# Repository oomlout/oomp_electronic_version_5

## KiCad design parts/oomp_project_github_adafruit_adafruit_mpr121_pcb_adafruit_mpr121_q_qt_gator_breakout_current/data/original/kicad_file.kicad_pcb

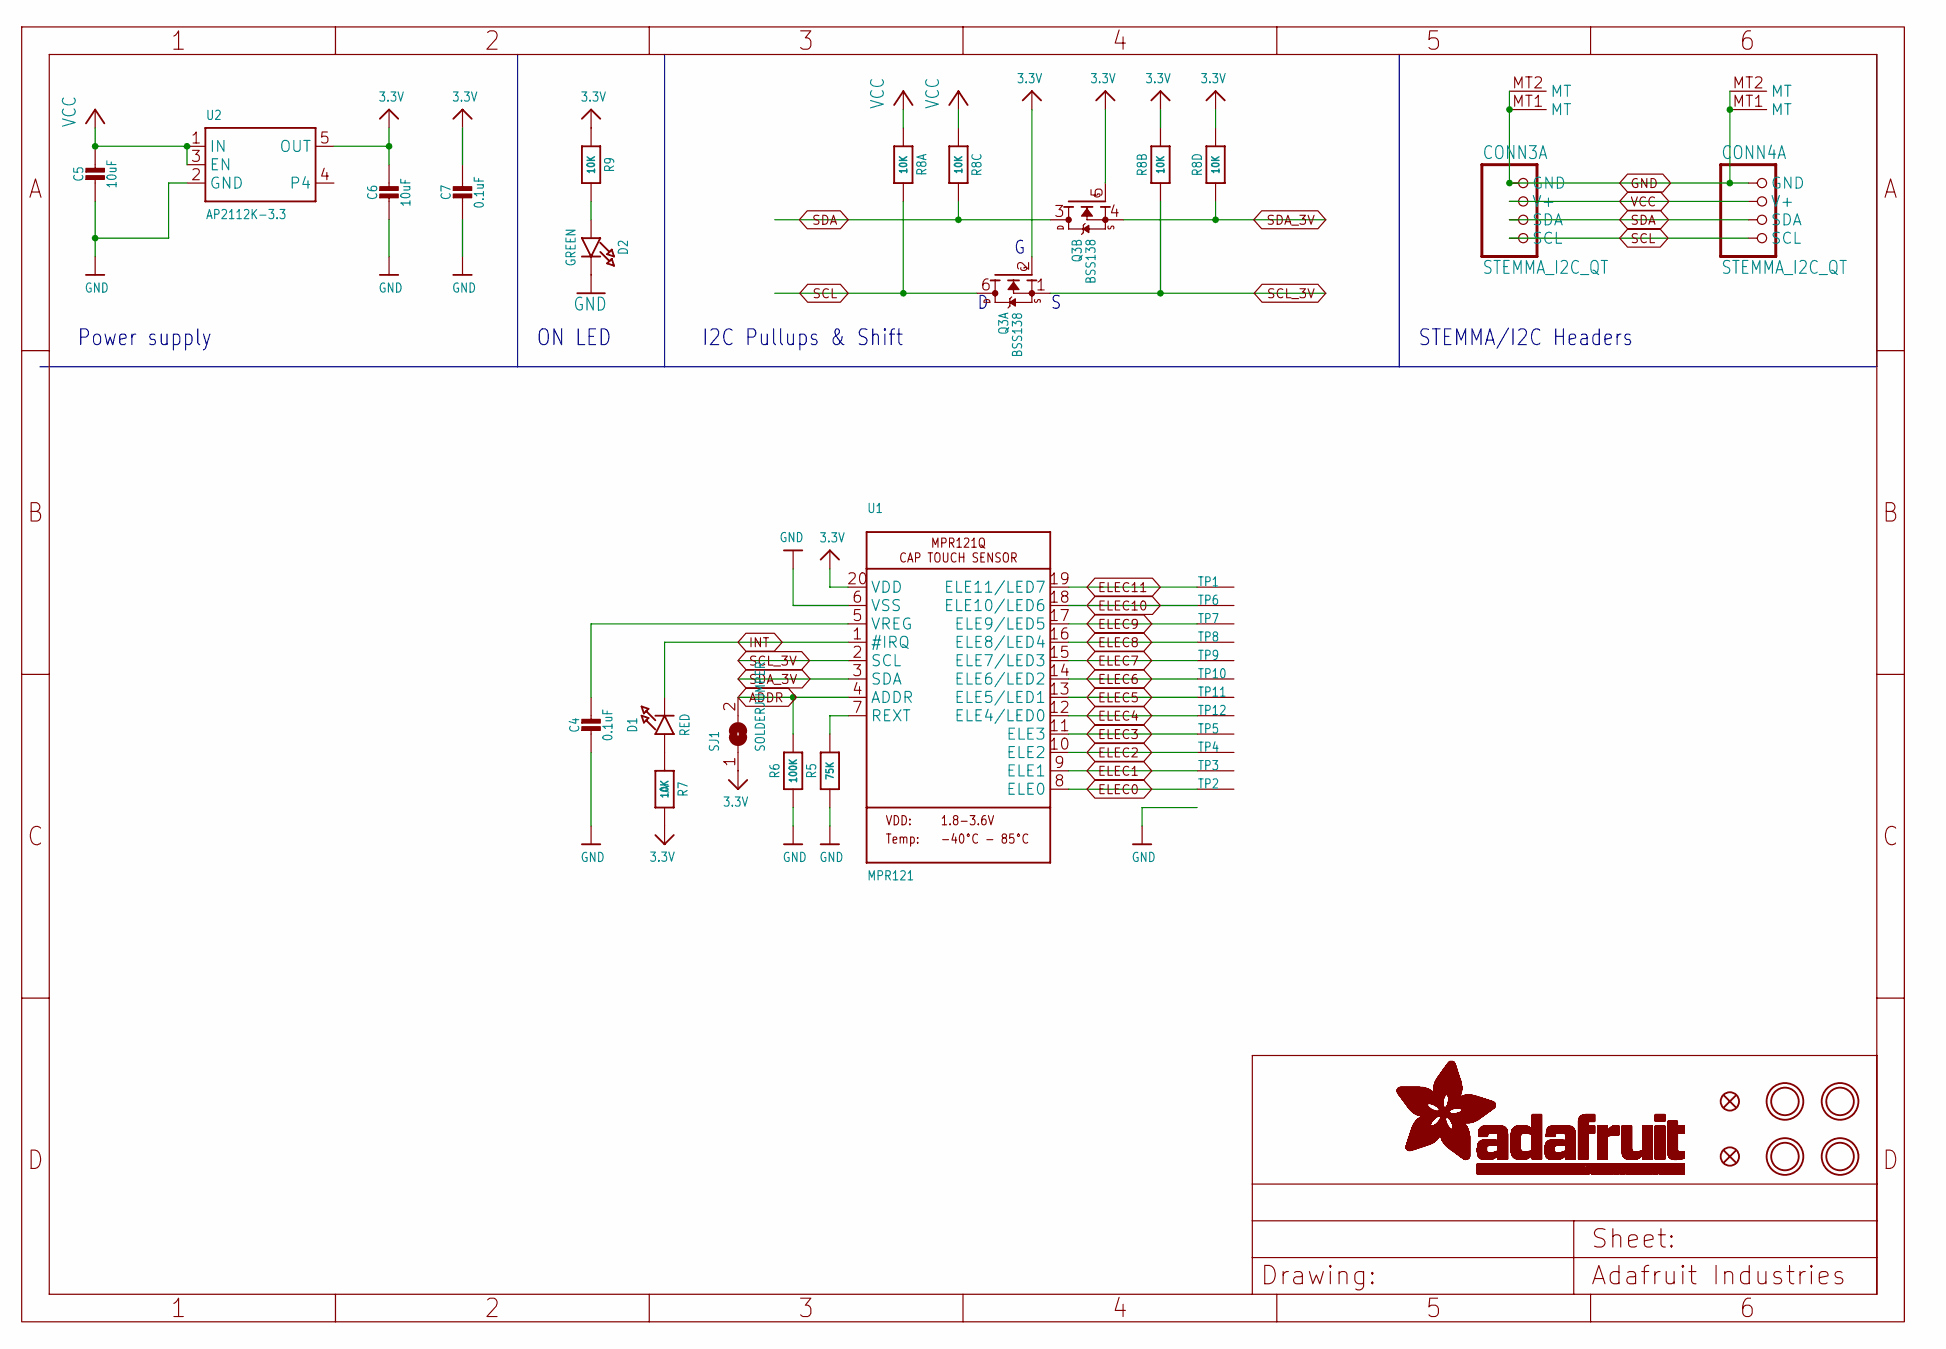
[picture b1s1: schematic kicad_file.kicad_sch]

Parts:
C4, C7: 0.1uF; 0603-NO
C5, C6: 10uF; 0805-NO
CONN3, CONN4: STEMMA_I2C_QT; JST_SH4
D1: RED; CHIPLED_0603_NOOUTLINE
D2: GREEN; CHIPLED_0603_NOOUTLINE
FID3, FID4: FIDUCIAL_1MM
Q3: BSS138; SOT363
R5: 75K; 0603-NO
R6: 100K; 0603-NO
R7, R9: 10K; 0603-NO
R8: 10K; RESPACK_4X0603
SJ1: SOLDERJUMPER; SOLDERJUMPER_ARROW_NOPASTE
TP1, TP2, TP3, TP4, TP5, TP6, TP7, TP8, TP9, TP10, TP11, TP12: SEWTAPPCB_ALLIGATOR; PCB_ALLI
U1: MPR121; QFN20_3MM_NOTHERMAL
U2: AP2112K-3.3; SOT23-5
U$7, U$8, U$34, U$35: MOUNTINGHOLE2.5; MOUNTINGHOLE_2.5_PLATED

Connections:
3.3V: C6.1, C7.1, Q3.2 (G), Q3.5 (G), R7.2, R8.2 (1), R8.4 (1), R9.1, SJ1.1, U1.20 (VDD), U2.5 (OUT)
ADDR: R6.2, SJ1.2, U1.4 (ADDR)
ELEC0: TP2.P$1, U1.8 (ELE0)
ELEC1: TP3.P$1, U1.9 (ELE1)
ELEC2: TP4.P$1, U1.10 (ELE2)
ELEC3: TP5.P$1, U1.11 (ELE3)
ELEC4: TP12.P$1, U1.12 (ELE4/LED0)
ELEC5: TP11.P$1, U1.13 (ELE5/LED1)
ELEC6: TP10.P$1, U1.14 (ELE6/LED2)
ELEC7: TP9.P$1, U1.15 (ELE7/LED3)
ELEC8: TP8.P$1, U1.16 (ELE8/LED4)
ELEC9: TP7.P$1, U1.17 (ELE9/LED5)
ELEC10: TP6.P$1, U1.18 (ELE10/LED6)
ELEC11: TP1.P$1, U1.19 (ELE11/LED7)
GND: C4.2, C5.2, C6.2, C7.2, CONN3.1 (GND), CONN3.MT1 (MT), CONN3.MT2 (MT), CONN4.1 (GND), CONN4.MT1 (MT), CONN4.MT2 (MT), D2.C, R5.1, R6.1, U1.6 (VSS), U2.2 (GND)
INT: D1.C, U1.1 (#IRQ)
unnamed: D1.A, R7.1
unnamed: C4.1, U1.5 (VREG)
unnamed: R5.2, U1.7 (REXT)
unnamed: D2.A, R9.2
SCL: CONN3.4 (SCL), CONN4.4 (SCL), Q3.6 (D), R8.8 (2)
SCL_3V: Q3.1 (S), R8.7 (2), U1.2 (SCL)
SDA: CONN3.3 (SDA), CONN4.3 (SDA), Q3.3 (D), R8.6 (2)
SDA_3V: Q3.4 (S), R8.5 (2), U1.3 (SDA)
VCC: C5.1, CONN3.2 (V+), CONN4.2 (V+), R8.1, R8.3 (1), U2.1 (IN), U2.3 (EN)

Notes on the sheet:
ON LED
I2C Pullups & Shift
STEMMA/I2C Headers
Power supply

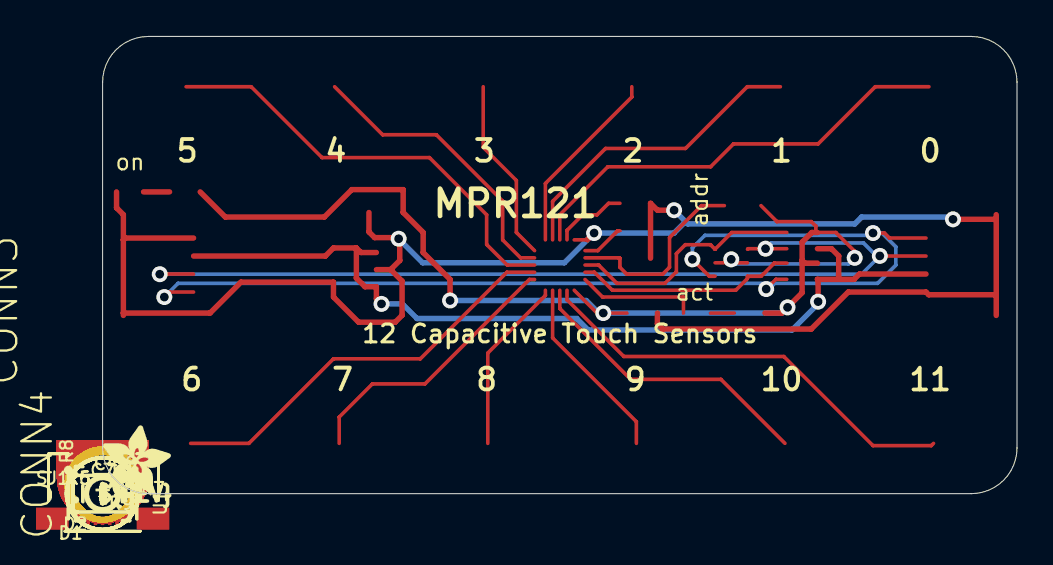
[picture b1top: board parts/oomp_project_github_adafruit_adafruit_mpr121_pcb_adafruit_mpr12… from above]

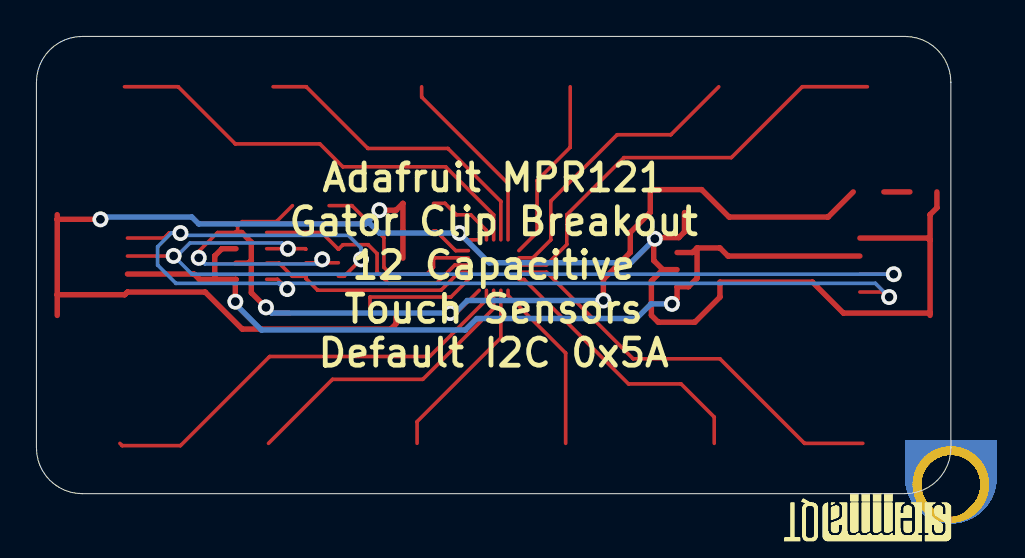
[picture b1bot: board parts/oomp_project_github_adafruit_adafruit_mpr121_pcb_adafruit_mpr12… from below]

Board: 2 copper layers, 50.8 x 25.4 mm, 39 parts (2 on the bottom side), 25 nets.

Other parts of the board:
U$10: PCBFEAT-REV-040
U$37: ADAFRUIT_3.5MM
U$39, U$40: STEMMAQT

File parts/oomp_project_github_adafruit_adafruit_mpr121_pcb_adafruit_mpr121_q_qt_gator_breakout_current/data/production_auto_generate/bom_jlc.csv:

Comment,Designator,Footprint,LCSC Part #
,U$37,Adafruit MPR121Q QT Gator Breakout-import-fps:ADAFRUIT_3.5MM,
,U$10,Adafruit MPR121Q QT Gator Breakout-import-fps:PCBFEAT-REV-040,
,"U$39,U$40",Adafruit MPR121Q QT Gator Breakout-import-fps:STEMMAQT,
0.1uF,"C4,C7",Adafruit MPR121Q QT Gator Breakout-import-fps:0603-NO,C14663
100K,R6,Adafruit MPR121Q QT Gator Breakout-import-fps:0603-NO,C25803
10K,"R7,R9",Adafruit MPR121Q QT Gator Breakout-import-fps:0603-NO,C98220
10K,R8,Adafruit MPR121Q QT Gator Breakout-import-fps:RESPACK_4X0603,C98220
10uF,"C5,C6",Adafruit MPR121Q QT Gator Breakout-import-fps:0805-NO,
75K,R5,Adafruit MPR121Q QT Gator Breakout-import-fps:0603-NO,C2907067
AP2112K-3.3,U2,Adafruit MPR121Q QT Gator Breakout-import-fps:SOT23-5,
BSS138,Q3,Adafruit MPR121Q QT Gator Breakout-import-fps:SOT363,
GREEN,D2,Adafruit MPR121Q QT Gator Breakout-import-fps:CHIPLED_0603_NOOUTLINE,
MPR121,U1,Adafruit MPR121Q QT Gator Breakout-import-fps:QFN20_3MM_NOTHERMAL,
RED,D1,Adafruit MPR121Q QT Gator Breakout-import-fps:CHIPLED_0603_NOOUTLINE,
STEMMA_I2C_QT,"CONN3,CONN4",Adafruit MPR121Q QT Gator Breakout-import-fps:JST_SH4,C160404

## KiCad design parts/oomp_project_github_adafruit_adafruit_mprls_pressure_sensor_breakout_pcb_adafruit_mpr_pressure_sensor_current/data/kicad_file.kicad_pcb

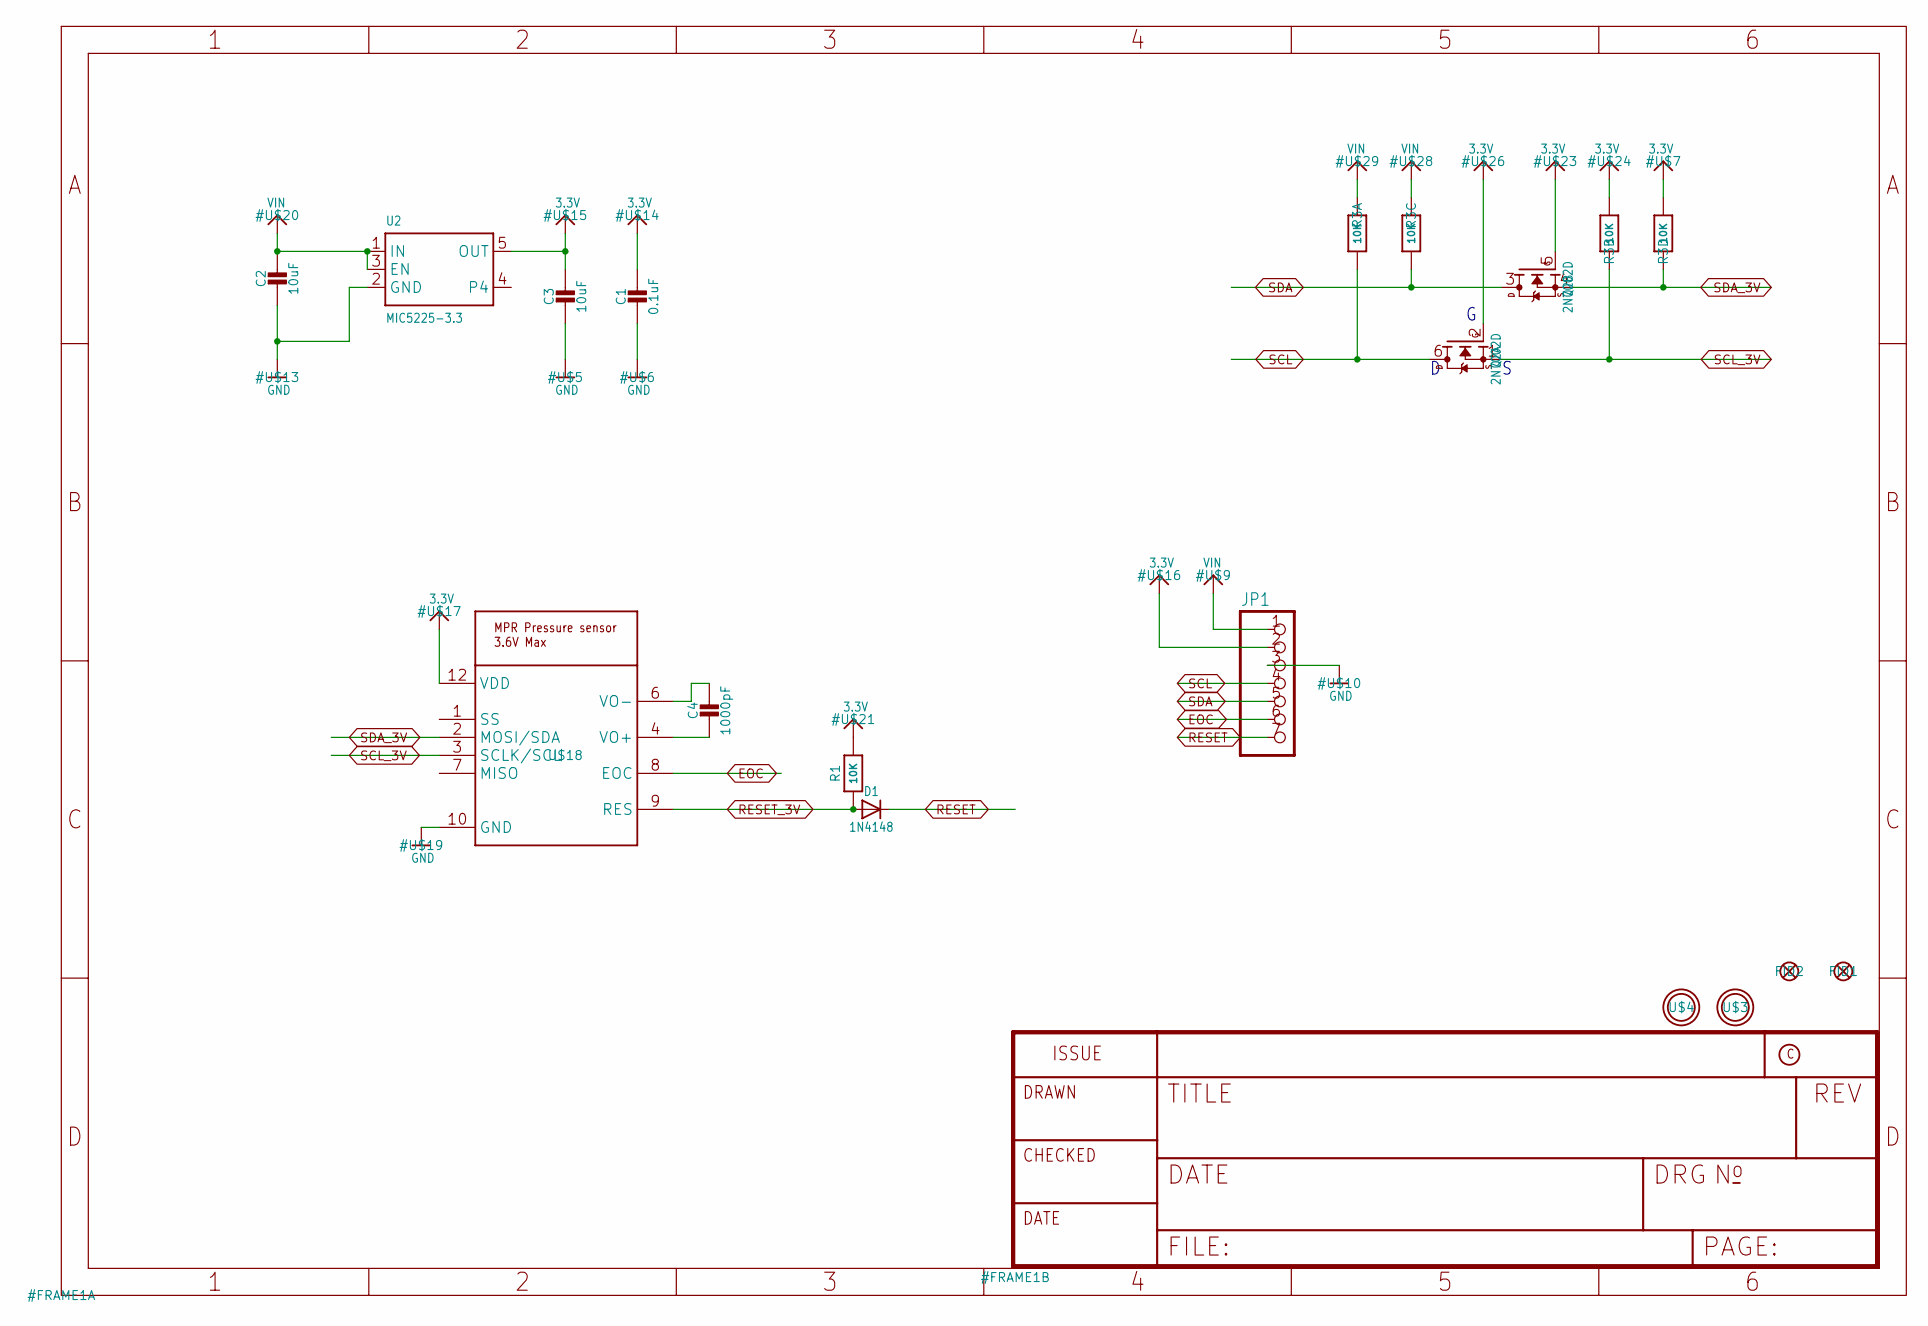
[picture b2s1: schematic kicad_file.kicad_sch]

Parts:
C1: 0.1uF; 0603-NO
C2, C3: 10uF; 0805-NO
C4: 1000pF; 0603-NO
D1: 1N4148; SOD-323
FID1, FID2: FIDUCIAL_1MM
JP1: HEADER-1X770MIL; 1X07_ROUND_70
Q2: 2N7002D; SOT363
R1: 10K; 0603-NO
R3: 10K; RESPACK_4X0603
U2: MIC5225-3.3; SOT23-5
U$3, U$4: MOUNTINGHOLE2.5; MOUNTINGHOLE_2.5_PLATED
U$18: MPR_SERIES_I2C_PRESSURE

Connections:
3.3V: C1.1, C3.1, JP1.2, Q2.2 (G), Q2.5 (G), R1.2, R3.2 (1), R3.4 (1), U2.5 (OUT), U$18.12 (VDD)
EOC: JP1.6, U$18.8 (EOC)
GND: C1.2, C2.2, C3.2, JP1.3, U2.2 (GND), U$18.10 (GND)
unnamed: C4.2, U$18.4 (VO+)
unnamed: C4.1, U$18.6 (VO-)
RESET: D1.C, JP1.7
RESET_3V: D1.A, R1.1, U$18.9 (RES)
SCL: JP1.4, Q2.6 (D), R3.8 (2)
SCL_3V: Q2.1 (S), R3.7 (2), U$18.3 (SCLK/SCL)
SDA: JP1.5, Q2.3 (D), R3.6 (2)
SDA_3V: Q2.4 (S), R3.5 (2), U$18.2 (MOSI/SDA)
VIN: C2.1, JP1.1, R3.1, R3.3 (1), U2.1 (IN), U2.3 (EN)

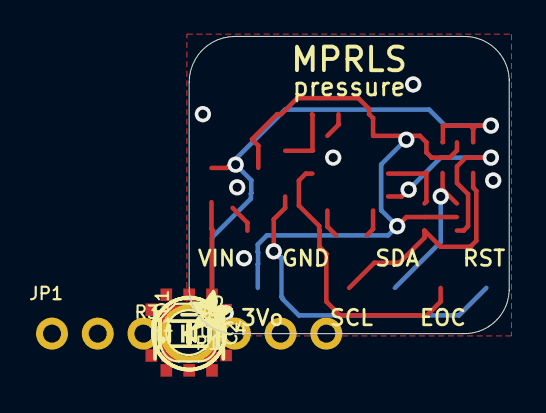
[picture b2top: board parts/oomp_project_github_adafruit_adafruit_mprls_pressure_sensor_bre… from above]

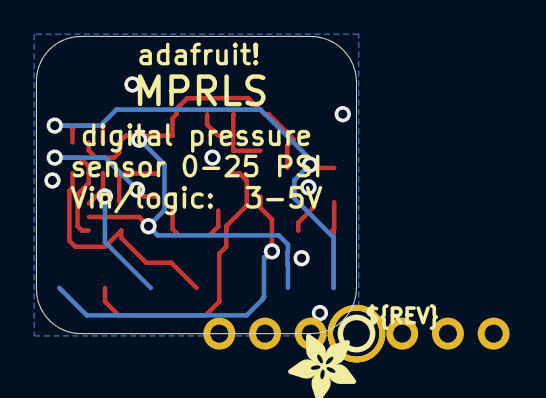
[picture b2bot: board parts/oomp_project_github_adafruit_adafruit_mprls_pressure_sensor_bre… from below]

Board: 2 copper layers, 17.8 x 16.5 mm, 18 parts (2 on the bottom side), 12 nets.

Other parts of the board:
U$1: ADAFRUIT_3.5MM
U$8: ADAFRUIT_2.5MM
U$27: PCBFEAT-REV-040

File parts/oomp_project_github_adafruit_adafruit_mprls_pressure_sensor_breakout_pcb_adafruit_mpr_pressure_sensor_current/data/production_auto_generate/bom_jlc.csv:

Comment,Designator,Footprint,LCSC Part #
,JP1,Adafruit MPR pressure sensor-import-fps:1X07_ROUND_70,C7501585
,U$8,Adafruit MPR pressure sensor-import-fps:ADAFRUIT_2.5MM,
,U$1,Adafruit MPR pressure sensor-import-fps:ADAFRUIT_3.5MM,
,U$27,Adafruit MPR pressure sensor-import-fps:PCBFEAT-REV-040,
0.1uF,C1,Adafruit MPR pressure sensor-import-fps:0603-NO,C14663
1000pF,C4,Adafruit MPR pressure sensor-import-fps:0603-NO,
10K,R1,Adafruit MPR pressure sensor-import-fps:0603-NO,C98220
10K,R3,Adafruit MPR pressure sensor-import-fps:RESPACK_4X0603,C98220
10uF,"C2,C3",Adafruit MPR pressure sensor-import-fps:0805-NO,
1N4148,D1,Adafruit MPR pressure sensor-import-fps:SOD-323,
2N7002D,Q2,Adafruit MPR pressure sensor-import-fps:SOT363,
MIC5225-3.3,U2,Adafruit MPR pressure sensor-import-fps:SOT23-5,
MPR_SERIES_I2C_PRESSURE,U$18,Adafruit MPR pressure sensor-import-fps:MPR_SERIES_I2C_PRESSURE,

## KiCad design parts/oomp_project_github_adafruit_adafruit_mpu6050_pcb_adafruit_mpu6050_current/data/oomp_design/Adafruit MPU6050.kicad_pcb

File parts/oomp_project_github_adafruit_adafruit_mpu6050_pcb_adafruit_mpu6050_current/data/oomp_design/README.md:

# OOMP KiCad design copy

Open `Adafruit MPU6050.kicad_pro` (or the `.kicad_pcb` / `.kicad_sch`) in KiCad. Local OOMP libraries are under `libraries/`. Original inputs are preserved in [../original/](../original/).

Only verified unchanged installed KiCad defaults were renamed. Modified, custom, unmatched and unavailable items remain unchanged. Soldering variants are never swapped during conversion. Existing pad coordinates, nets and UUIDs are preserved.

See [conversion_report.yaml](conversion_report.yaml) for every conversion and skip. Copy this directory before editing; regeneration refuses to overwrite edited design files.

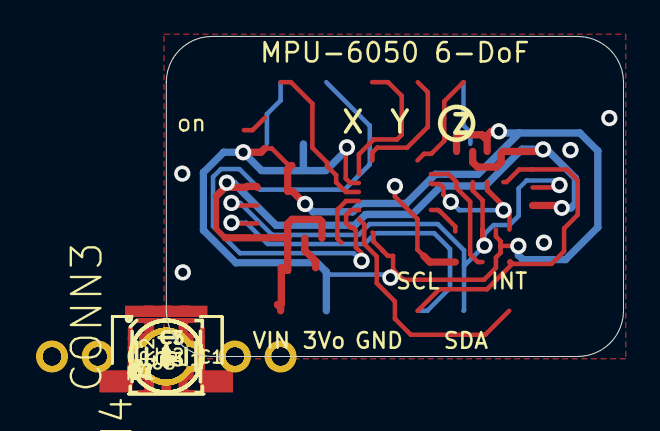
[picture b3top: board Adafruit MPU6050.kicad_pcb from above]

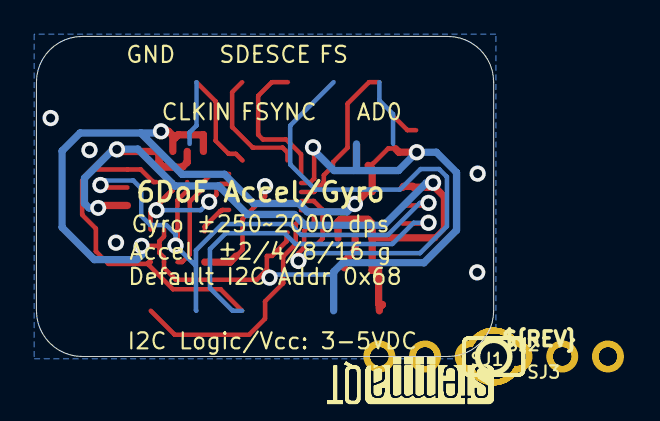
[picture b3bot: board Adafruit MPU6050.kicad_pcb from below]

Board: 2 copper layers, 25.4 x 17.8 mm, 28 parts (6 on the bottom side), 16 nets.

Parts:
C1: 2.2nF; 0603-NO
C2, C7: 0.1uF; 0603-NO
C5, C6: 10uF; 0805-NO
CONN3, CONN4: STEMMA_I2C_QT; JST_SH4
D1: GREEN; CHIPLED_0603_NOOUTLINE
FID3, FID4: FIDUCIAL_1MM
JP2: 1X06_ROUND
JP3: 1X06_ROUND_70
Q2: BSS138; SOT363
R2, R4: 10K; 0603-NO
R3: 10K; RESPACK_4X0603
SJ1: CLKIN; SOLDERJUMPER_CLOSEDWIRE
SJ2: FSYNC; SOLDERJUMPER_CLOSEDWIRE
SJ3: SOLDERJUMPER_ARROW_NOPASTE
U1: MPU-6050; QFN24_4MM_SMSC
U3: AP2112K-3.3; SOT23-5
U$39, U$40, U$42, U$43: MOUNTINGHOLE2.5; MOUNTINGHOLE_2.5_PLATED
U$46: PCBFEAT-REV-040
U$47, U$48: STEMMAQT

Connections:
3.3V: C6.1, C7.1, JP3.2, Q2.2, Q2.5, R3.2, R3.4, R4.1, SJ3.1, U1.8, U1.13, U3.5
AD0: JP2.1, R2.1, SJ3.2, U1.9
CLKIN: JP2.5, SJ1.2, U1.1
CPOUT: C1.1, U1.20
FSYNC_IN: JP2.2, SJ2.2, U1.11
GND: C1.2, C2.2, C5.2, C6.2, C7.2, CONN3.1, CONN4.1, D1.C, JP2.6, JP3.3, R2.2, SJ1.1, SJ2.1, U1.18, U1.THERM, U3.2
INT: JP3.6, U1.12
unnamed: D1.A, R4.2
REGOUT: C2.1, U1.10
SCL: CONN3.4, CONN4.4, JP3.4, Q2.6, R3.8
SCL_3V: Q2.1, R3.7, U1.23
SCL_EXT: JP2.3, U1.7
SDA: CONN3.3, CONN4.3, JP3.5, Q2.3, R3.6
SDA_3V: Q2.4, R3.5, U1.24
SDA_EXT: JP2.4, U1.6
VCC: C5.1, CONN3.2, CONN4.2, JP3.1, R3.1, R3.3, U3.1, U3.3

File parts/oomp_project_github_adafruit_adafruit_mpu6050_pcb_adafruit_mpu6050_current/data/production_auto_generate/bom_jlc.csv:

Comment,Designator,Footprint,LCSC Part #
,JP2,Adafruit MPU6050-import-fps:1X06_ROUND,C37208
,JP3,Adafruit MPU6050-import-fps:1X06_ROUND_70,C37208
,U$46,Adafruit MPU6050-import-fps:PCBFEAT-REV-040,
,"U$47,U$48",Adafruit MPU6050-import-fps:STEMMAQT,
0.1uF,"C2,C7",Adafruit MPU6050-import-fps:0603-NO,C14663
10K,"R2,R4",Adafruit MPU6050-import-fps:0603-NO,C98220
10K,R3,Adafruit MPU6050-import-fps:RESPACK_4X0603,C98220
10uF,"C5,C6",Adafruit MPU6050-import-fps:0805-NO,
2.2nF,C1,Adafruit MPU6050-import-fps:0603-NO,
AP2112K-3.3,U3,Adafruit MPU6050-import-fps:SOT23-5,
BSS138,Q2,Adafruit MPU6050-import-fps:SOT363,
GREEN,D1,Adafruit MPU6050-import-fps:CHIPLED_0603_NOOUTLINE,
MPU-6050,U1,Adafruit MPU6050-import-fps:QFN24_4MM_SMSC,
STEMMA_I2C_QT,"CONN3,CONN4",Adafruit MPU6050-import-fps:JST_SH4,C160404

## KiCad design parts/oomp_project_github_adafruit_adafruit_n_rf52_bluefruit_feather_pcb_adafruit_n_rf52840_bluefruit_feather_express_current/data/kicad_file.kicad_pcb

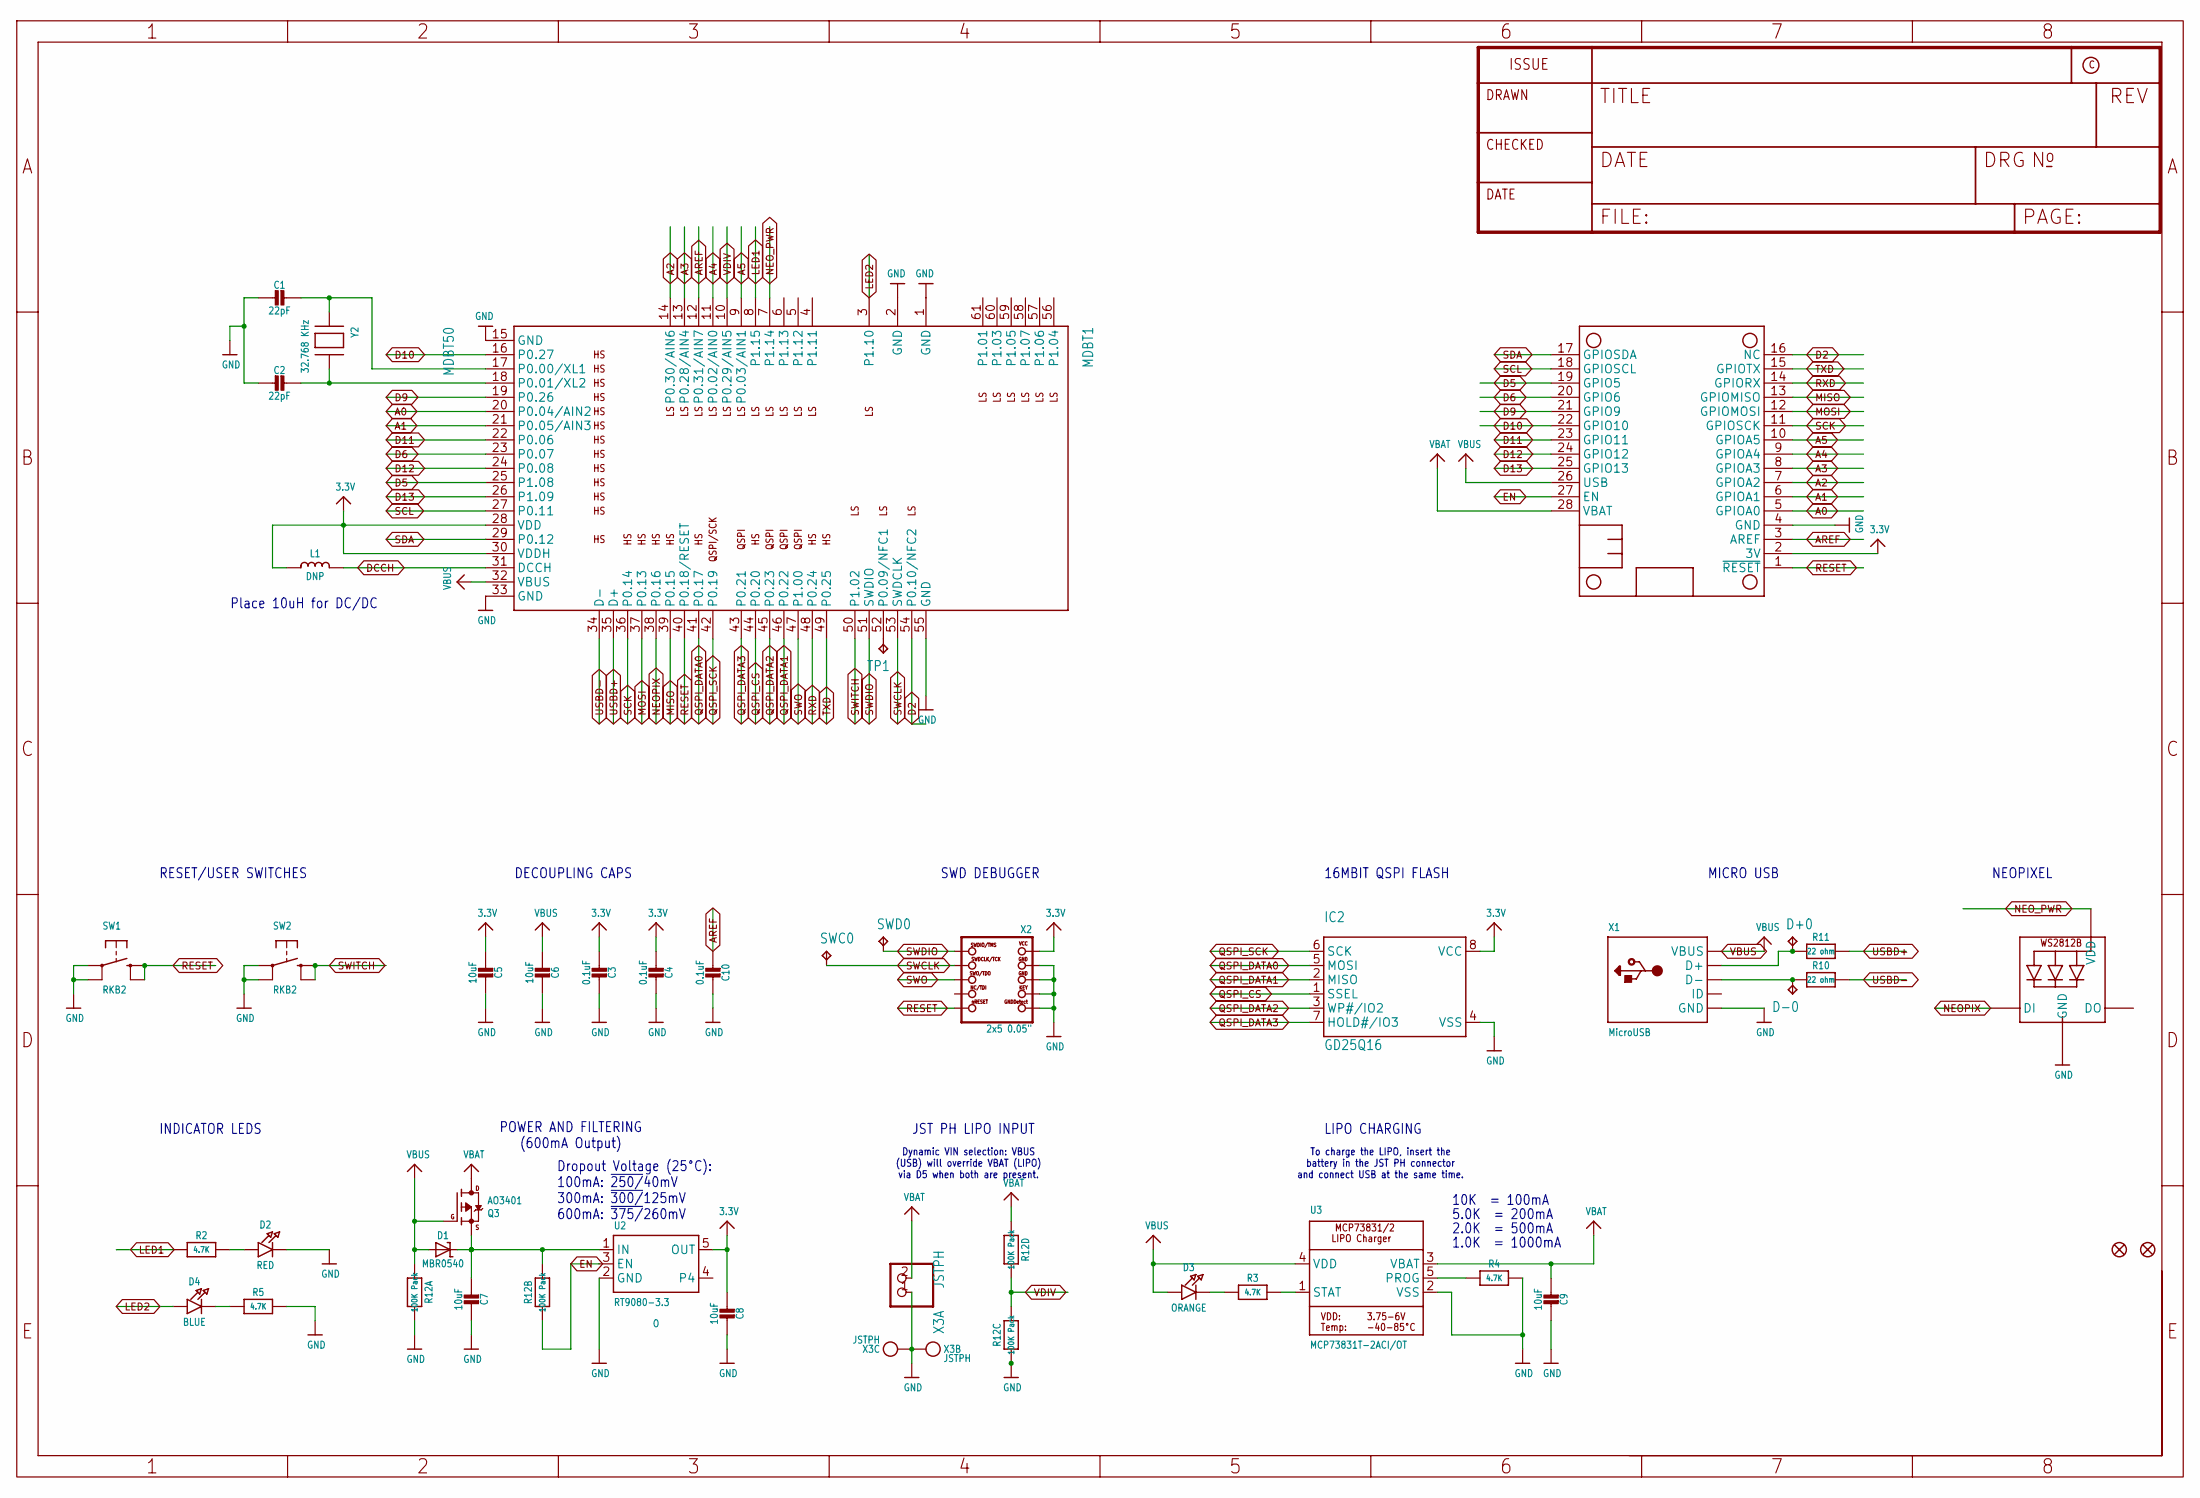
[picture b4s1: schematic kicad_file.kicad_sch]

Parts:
C1, C2: 22pF; 0603-NO
C3, C4, C10: 0.1uF; 0603-NO
C5, C6, C7, C8, C9: 10uF; 0805-NO
D1: MBR0540; SOD-123
D2: RED; CHIPLED_0603_NOOUTLINE
D3: ORANGE; CHIPLED_0603_NOOUTLINE
D4: BLUE; CHIPLED_0603_NOOUTLINE
D+0: TPTP10R; TP10R
D-0: TPTP10R; TP10R
FID1, FID2: FIDUCIAL_1MM
IC2: GD25Q16; USON8
L1: DNP; _0805MP
LED1: WS2812B_3535FULL; LED3535_FULLPADS
MDBT1: MDBT50
MS1: FEATHERWING_NODIM
Q3: AO3401; SOT23-R
R2, R3, R4, R5: 4.7K; 0603-NO
R10, R11: 22 ohm; _0603MP
R12: 100K Pack; RESPACK_4X0603
SW1, SW2: RKB2; BTN_RKB2_4.6X2.8
SWC0: TPTP12R; TP12R
SWD0: TPTP12R; TP12R
TP1: TPTP10R; TP10R
U2: RT9080-3.3; SOT23-5; JLC_ROTATION 0
U3: MCP73831T-2ACI/OT; SOT23-5; JLC_ROTATION 0
X1: MicroUSB; 4UCONN_20329_V2
X2: 2x5 0.05"; 2X05_1.27MM_BOX_POSTS
X3: JSTPH; JSTPH2_BATT; LCSC C47647
Y2: 32.768 KHz; XTAL3215

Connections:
3.3V: C3.2, C4.2, C5.2, C8.2, IC2.8 (VCC), L1.1, MDBT1.28 (VDD), MDBT1.30 (VDDH), MS1.2 (3V), U2.5 (OUT), X2.1 (VCC)
A0: MDBT1.20 (P0.04/AIN2), MS1.5 (GPIOA0)
A1: MDBT1.21 (P0.05/AIN3), MS1.6 (GPIOA1)
A2: MDBT1.14 (P0.30/AIN6), MS1.7 (GPIOA2)
A3: MDBT1.13 (P0.28/AIN4), MS1.8 (GPIOA3)
A4: MDBT1.11 (P0.02/AIN0), MS1.9 (GPIOA4)
A5: MDBT1.9 (P0.03/AIN1), MS1.10 (GPIOA5)
AREF: C10.2, MDBT1.12 (P0.31/AIN7), MS1.3 (AREF)
D2: MDBT1.54 (P0.10/NFC2), MS1.16 (NC)
D5: MDBT1.25 (P1.08), MS1.19 (GPIO5)
D6: MDBT1.23 (P0.07), MS1.20 (GPIO6)
D9: MDBT1.19 (P0.26), MS1.21 (GPIO9)
D10: MDBT1.16 (P0.27), MS1.22 (GPIO10)
D11: MDBT1.22 (P0.06), MS1.23 (GPIO11)
D12: MDBT1.24 (P0.08), MS1.24 (GPIO12)
D13: MDBT1.26 (P1.09), MS1.25 (GPIO13)
D+: D+0.TP, R11.1, X1.D+
D-: D-0.TP, R10.1, X1.D-
DCCH: L1.2, MDBT1.31 (DCCH)
EN: MS1.27 (EN), R12.2 (1), U2.3 (EN)
GND: C1.2, C2.2, C3.1, C4.1, C5.1, C6.1, C7.1, C8.1, C9.1, C10.1, D2.C, IC2.4 (VSS), LED1.4 (GND), MDBT1.1 (GND), MDBT1.2 (GND), MDBT1.15 (GND), MDBT1.33 (GND), MDBT1.55 (GND), MS1.4 (GND), R4.2, R5.2, R12.3 (1), R12.8 (2), SW1.A, SW1.A' (P1), SW2.A, SW2.A' (P1), U2.2 (GND), U3.2 (VSS), X1.BASE@1 (GND), X1.BASE@2 (GND), X1.GND, X1.SPRT@1 (GND), X1.SPRT@2 (GND), X1.SPRT@3 (GND), X1.SPRT@4 (GND), X2.3 (GND), X2.5 (GND), X2.7 (KEY), X2.9 (GNDDETECT), X3.1, X3.NC1, X3.NC2
LED1: MDBT1.8 (P1.15), R2.1
LED2: D4.A, MDBT1.3 (P1.10)
MISO: MDBT1.39 (P0.15), MS1.13 (GPIOMISO)
MOSI: MDBT1.37 (P0.13), MS1.12 (GPIOMOSI)
unnamed: D3.C, R3.1
unnamed: D2.A, R2.2
unnamed: C1.1, MDBT1.17 (P0.00/XL1), Y2.P$1
unnamed: C2.1, MDBT1.18 (P0.01/XL2), Y2.P$2
unnamed: R3.2, U3.1 (STAT)
unnamed: R4.1, U3.5 (PROG)
unnamed: D4.C, R5.1
NEOPIX: LED1.1 (DI), MDBT1.38 (P0.16)
NEO_PWR: LED1.2 (VDD), MDBT1.7 (P1.14)
NFC2: MDBT1.52 (P0.09/NFC1), TP1.TP
QSPI_CS: IC2.1 (SSEL), MDBT1.44 (P0.20)
QSPI_DATA0: IC2.5 (MOSI), MDBT1.41 (P0.17)
QSPI_DATA1: IC2.2 (MISO), MDBT1.46 (P0.22)
QSPI_DATA2: IC2.3 (WP#/IO2), MDBT1.45 (P0.23)
QSPI_DATA3: IC2.7 (HOLD#/IO3), MDBT1.43 (P0.21)
QSPI_SCK: IC2.6 (SCK), MDBT1.42 (P0.19)
RESET: MDBT1.40 (P0.18/RESET), MS1.1 (~RESET), SW1.B (S), SW1.B' (S1), X2.10 (NRESET)
RXD: MDBT1.48 (P0.24), MS1.14 (GPIORX)
SCK: MDBT1.36 (P0.14), MS1.11 (GPIOSCK)
SCL: MDBT1.27 (P0.11), MS1.18 (GPIOSCL)
SDA: MDBT1.29 (P0.12), MS1.17 (GPIOSDA)
SWCLK: MDBT1.53 (SWDCLK), SWC0.TP, X2.4 (SWDCLK)
SWDIO: MDBT1.51 (SWDIO), SWD0.TP, X2.2 (SWDIO)
SWITCH: MDBT1.50 (P1.02), SW2.B (S), SW2.B' (S1)
SWO: MDBT1.47 (P1.00), X2.6 (SWO)
TXD: MDBT1.49 (P0.25), MS1.15 (GPIOTX)
USBD+: MDBT1.35 (D+), R11.2
USBD-: MDBT1.34 (D-), R10.2
VBAT: C9.2, MS1.28 (VBAT), Q3.3 (D), R12.4 (1), U3.3 (VBAT), X3.2
VBUS: C6.2, D1.A, D3.A, MDBT1.32 (VBUS), MS1.26 (USB), Q3.1 (G), R12.1, U3.4 (VDD), X1.VBUS
VDIV: MDBT1.10 (P0.29/AIN5), R12.5 (2), R12.6 (2)
VHI: C7.2, D1.C, Q3.2 (S), R12.7 (2), U2.1 (IN)

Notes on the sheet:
NEOPIXEL
Dynamic VIN selection: VBUS (USB) will override VBAT (LIPO) via D5 when both are present.
SWD DEBUGGER
Dropout Voltage (25°C): 100mA: ~{250/}40mV 300mA: ~{300/}125mV 600mA: ~{375/}260mV
10K = 100mA
RESET/USER SWITCHES
INDICATOR LEDS
MICRO USB
DECOUPLING CAPS
To charge the LIPO, insert the battery in the JST PH connector and connect USB at the same time.
JST PH LIPO INPUT
LIPO CHARGING
POWER AND FILTERING (600mA Output)
16MBIT QSPI FLASH
Place 10uH for DC/DC
2.0K = 500mA
1.0K = 1000mA
5.0K = 200mA

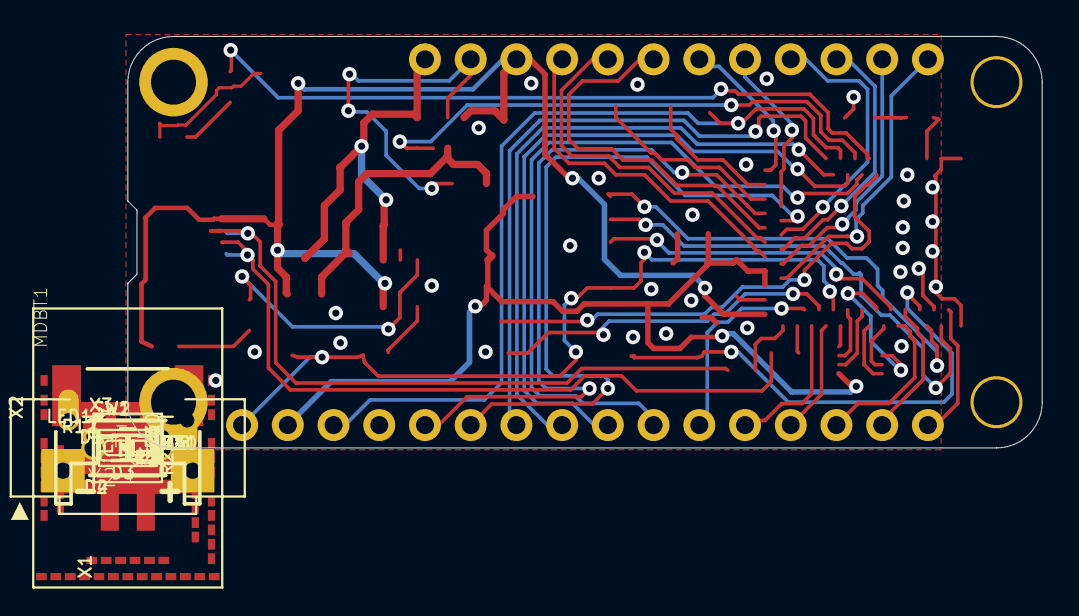
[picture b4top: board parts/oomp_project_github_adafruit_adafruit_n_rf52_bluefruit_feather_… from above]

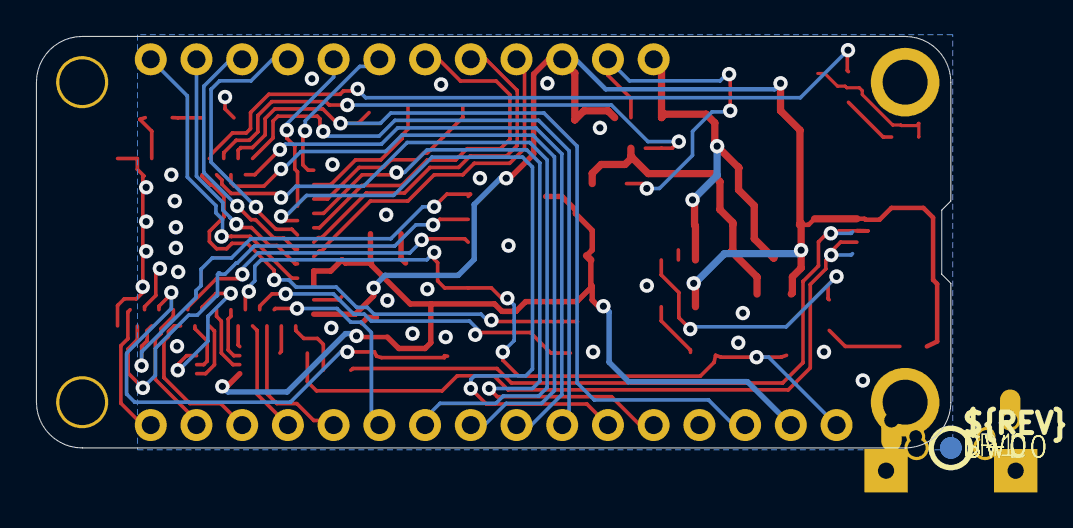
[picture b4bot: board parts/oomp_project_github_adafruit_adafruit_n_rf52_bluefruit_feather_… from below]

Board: 2 copper layers, 50.8 x 22.9 mm, 45 parts (7 on the bottom side), 57 nets.

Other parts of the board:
U$10: PCBFEAT-REV-056
U$12: NRF52840_BOT
U$14: NRF52840_TOP
